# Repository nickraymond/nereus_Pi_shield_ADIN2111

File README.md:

# nereus_Pi_shield_ADIN2111

A Raspberry Pi Zero 2W shield built from a copy of the Sofar Bristlemouth mote:
ADIN2111 two-port 10BASE-T1L with PoDL, powered from the bus, 5 V for the Pi,
a 24 V payload port, and the Sofar mote's power path unchanged except the payload load switch (D17) (~20 W absolute
max, 890 mA per port inductor at 24 V; 50 W in a later revision). Potted.

Claude Code does the schematic capture, up to a design-review package. Nick
reviews, lays out, routes and brings up the board.

## Folders

```
Nereus_Pi_Shield_Adin2111/   live KiCad 10 project, the board ordered at JLC — open Nereus_Pi_Shield_Adin2111.kicad_pro
docs/                        spec, tracker, design log, power-path study
docs/design-review/          ERC, netlist, PDF and the review package
KiCAD_reference_designs/     BM mote 000639-AB, UrchinCam (read-only)
Archive/                     earlier iterations, junction fix (read-only)
pi-shield-checklist.html     shared visual view of docs/TRACKER.md (open in a browser)
```

## Working on it

- Agents: start with `CLAUDE.md`, then `/agent-entry`.
- People: `docs/TRACKER.md` shows where things stand; `docs/SPEC.md` says what
  we're building and why.
- Close KiCad before an agent edits the project.

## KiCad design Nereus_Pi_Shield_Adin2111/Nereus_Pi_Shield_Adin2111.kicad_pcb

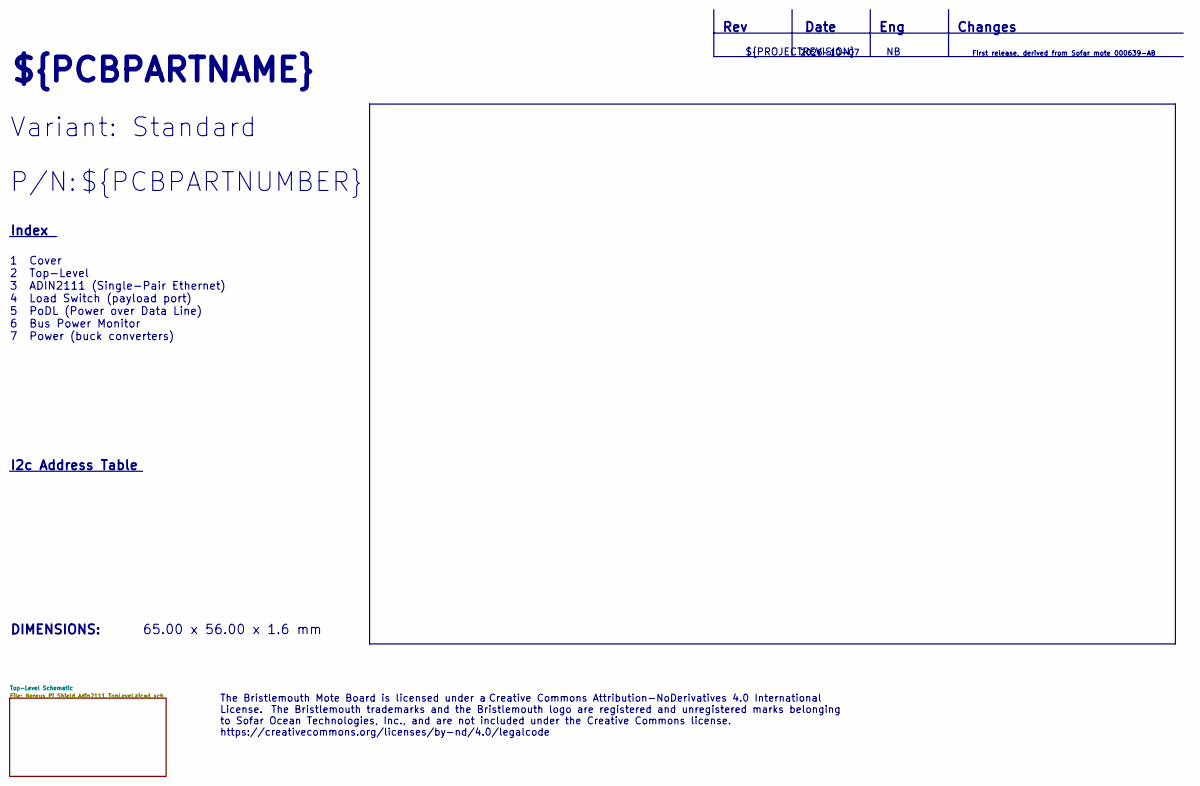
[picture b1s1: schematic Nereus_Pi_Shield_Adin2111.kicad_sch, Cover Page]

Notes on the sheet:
Variant: Standard
Date
${PCBPARTNAME}
Changes
${PCBPARTNUMBER}
First release, derived from Sofar mote 000639-AB
Index
2026-10-07
${PROJECTREVISION}
Rev
I2c Address Table
Eng
65.00 x 56.00 x 1.6 mm
1 Cover 2 Top-Level 3 ADIN2111 (Single-Pair Ethernet) 4 Load Switch (payload port) 5 PoDL (Power over Data Line) 6 Bus Power Monitor 7 Power (buck converters)
P/N:
DIMENSIONS:
The Bristlemouth Mote Board is licensed under a Creative Commons Attribution-NoDerivatives 4.0 International License. The Bristlemouth trademarks and the Bristlemouth logo are registered and unregistered marks belonging to Sofar Ocean Technologies, Inc., and are not included under the Creative Comm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

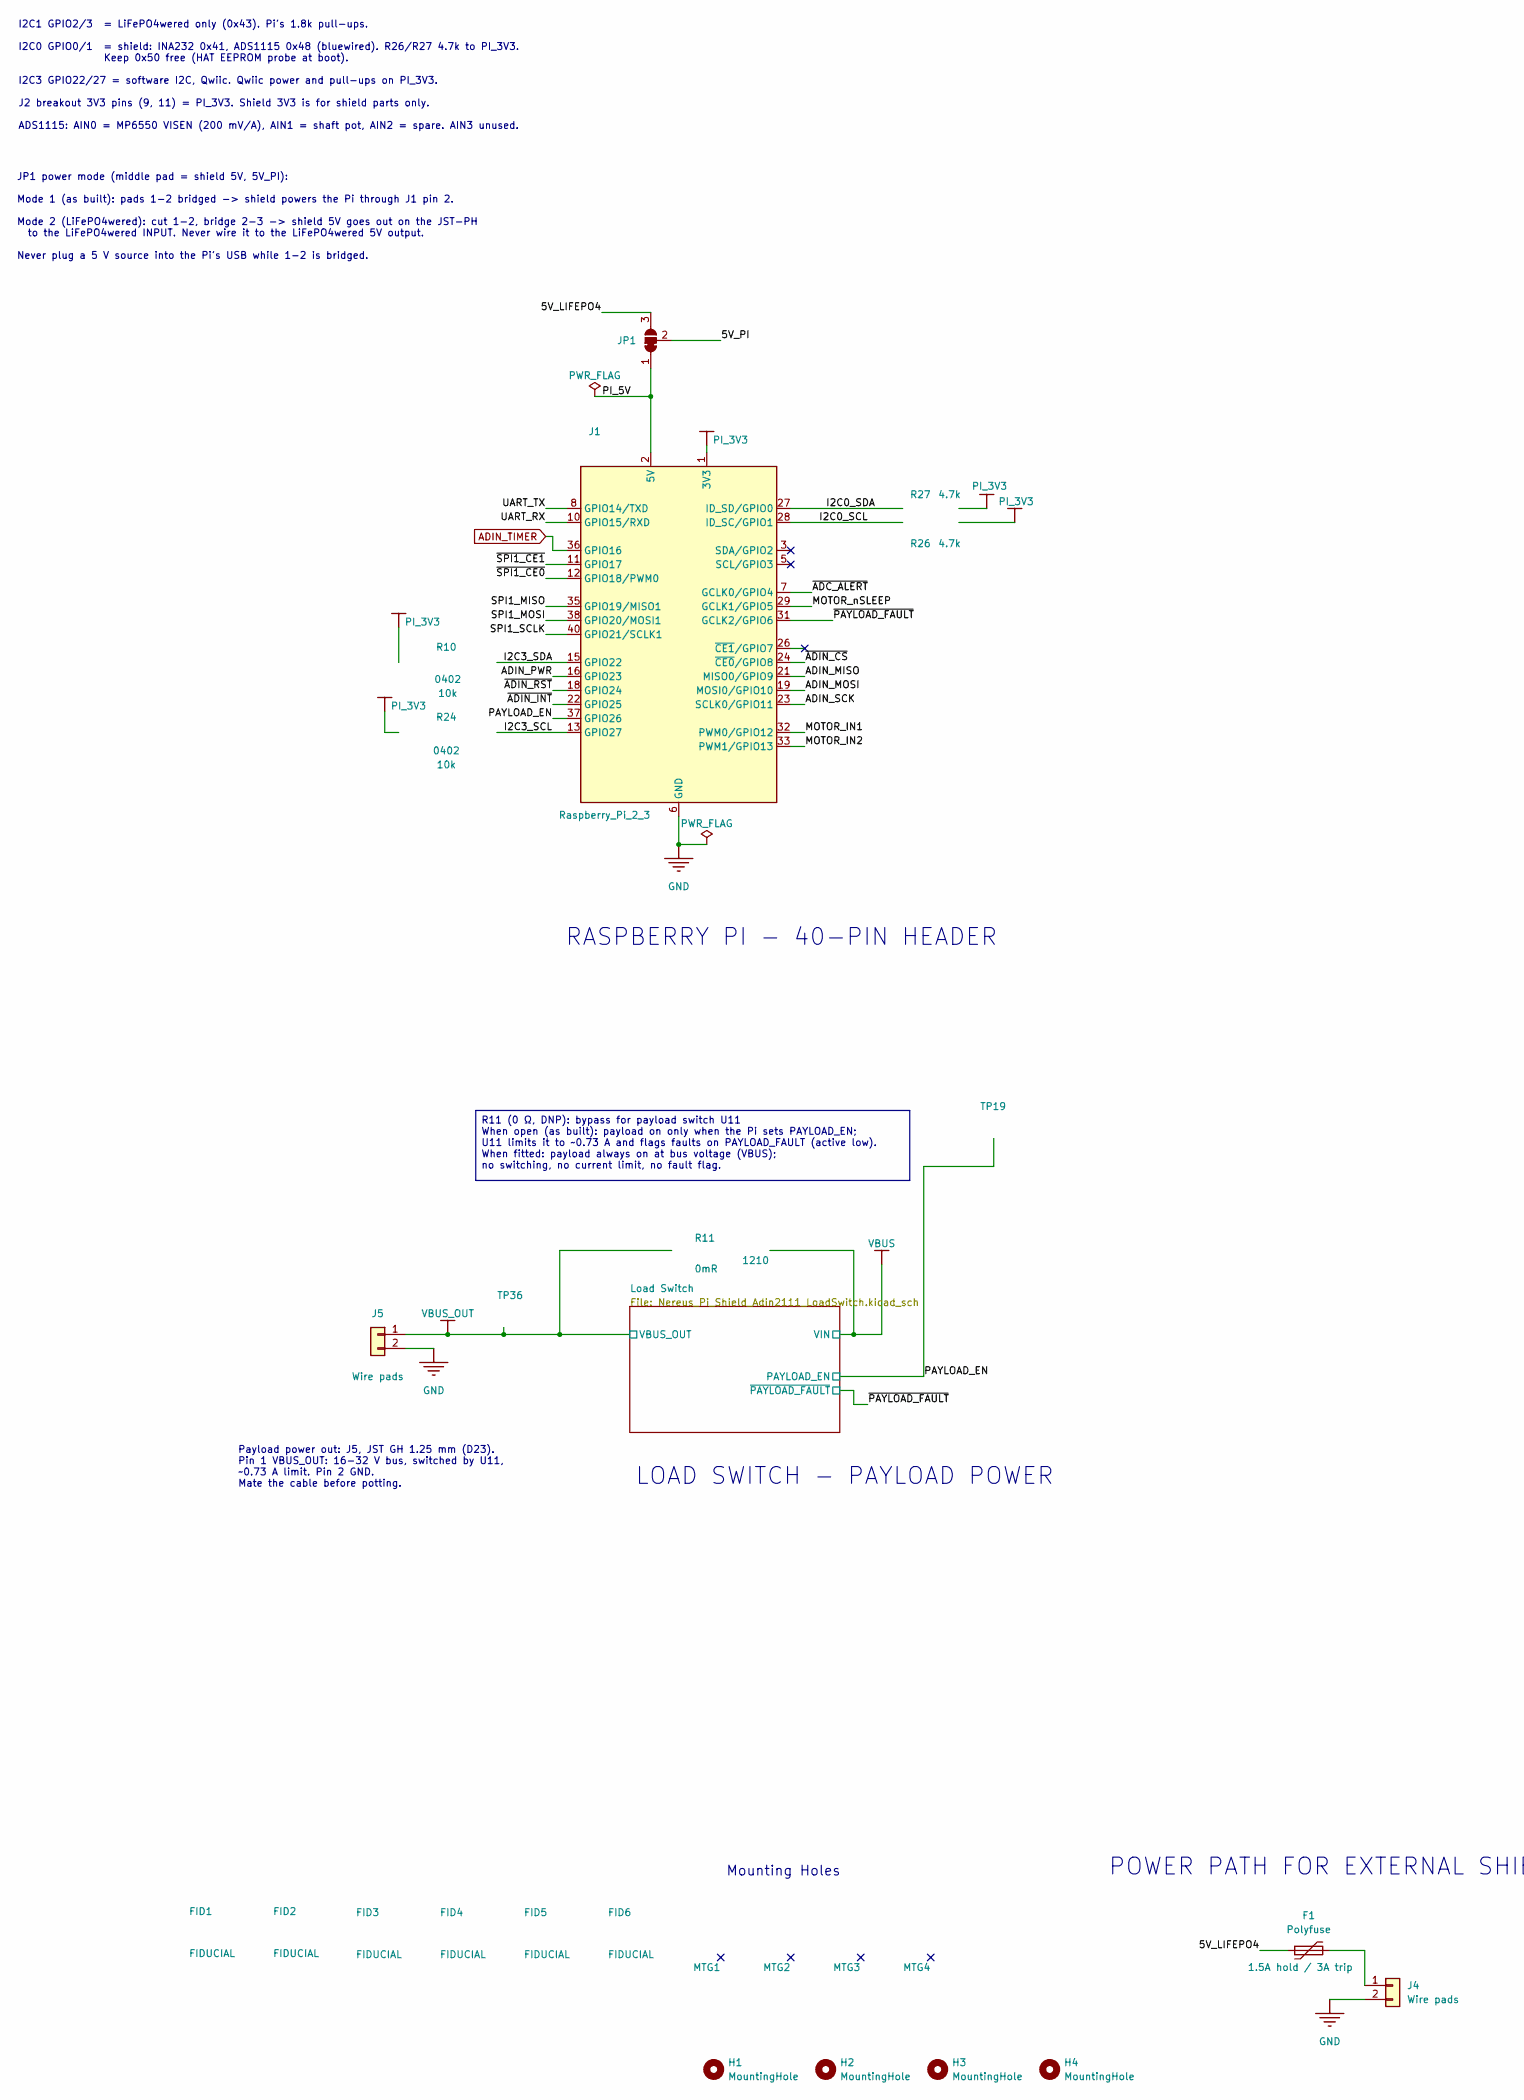
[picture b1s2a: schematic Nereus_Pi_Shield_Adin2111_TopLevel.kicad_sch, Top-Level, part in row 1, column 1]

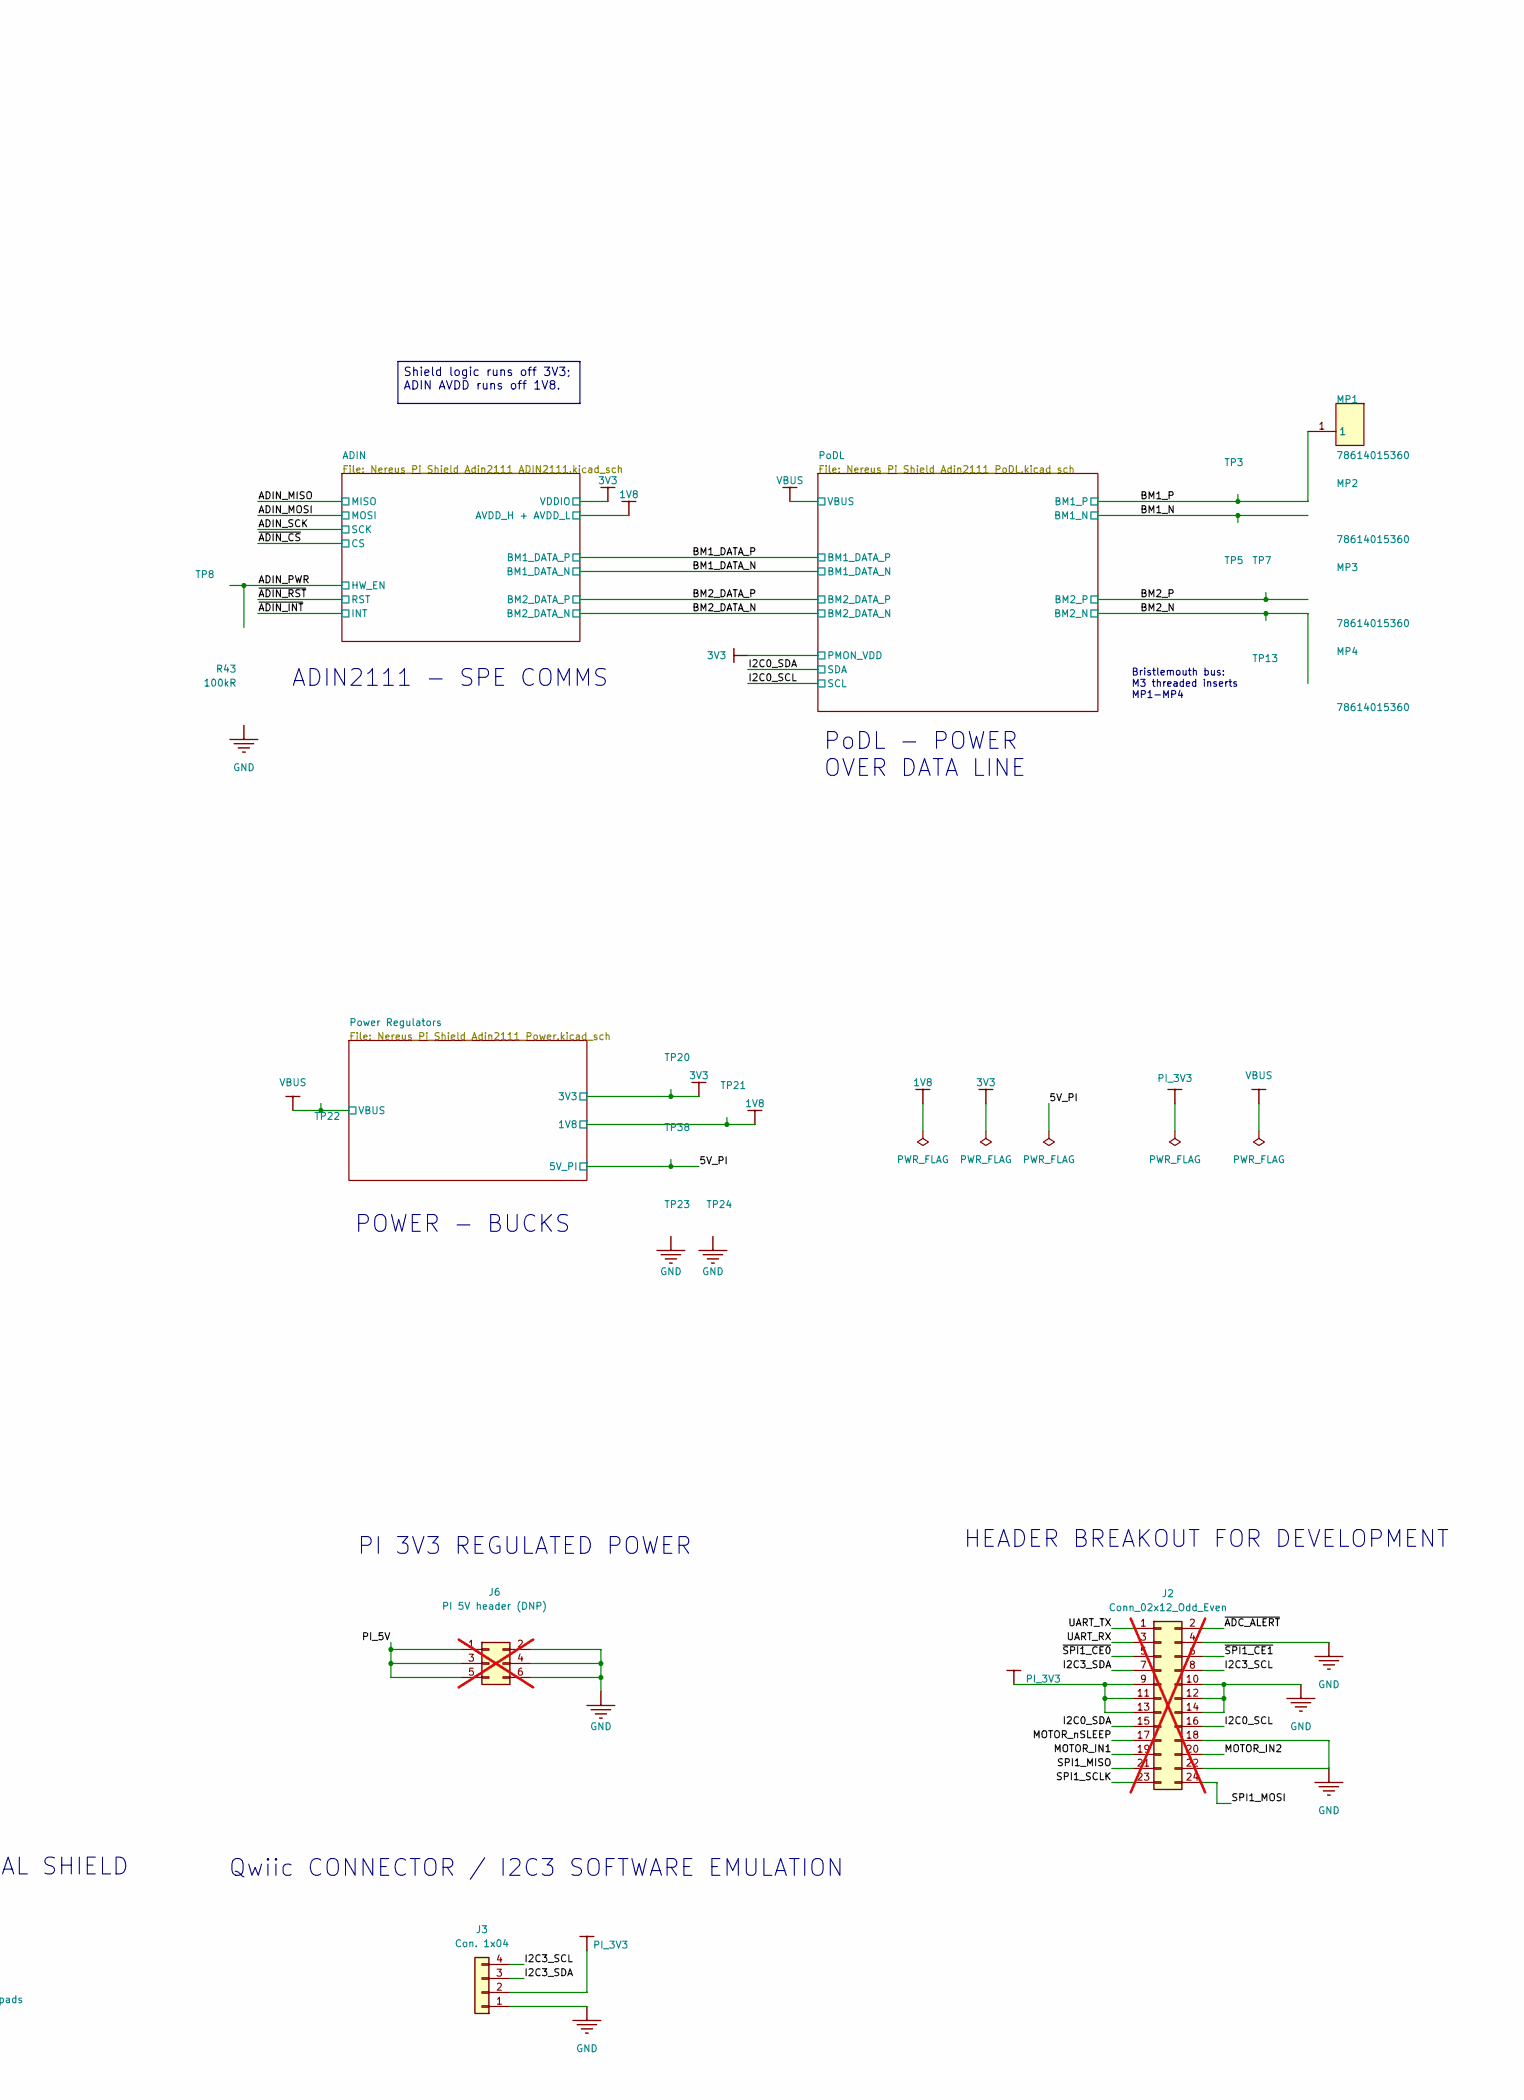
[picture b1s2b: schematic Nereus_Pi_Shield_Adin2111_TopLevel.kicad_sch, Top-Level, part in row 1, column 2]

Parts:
F1: Polyfuse; Fuse_1206_3216Metric
FID1, FID2, FID3, FID4, FID5, FID6: FIDUCIAL; FIDUCIAL_075MM
H1, H2, H3, H4: MountingHole; MountingHole_2.7mm_M2.5_ISO7380
J1: Raspberry_Pi_2_3; PinSocket_2x20_P2.54mm_Vertical
J2: Conn_02x12_Odd_Even; PinHeader_2x12_P2.54mm_Vertical; not fitted
J3: Con. 1x04; JST_SH_SM04B-SRSS-TB_1x04-1MP_P1.00mm_Horizontal
J4, J5: Wire pads; WirePads_1x02_P3.81mm_Oval4.2x2.6mm_Drill1.3mm
J6: PI 5V header (DNP); PinHeader_2x03_P2.54mm_Vertical; not fitted
JP1: SolderJumper_3_Bridged12; SolderJumper-3_P1.3mm_Bridged12_RoundedPad1.0x1.5mm
MP1, MP2, MP3, MP4: 78614015360; 78614015360-Footprint-2; MANUFACTURER PART NUMBER 78614015360
MTG1, MTG2, MTG3, MTG4: Hole_M3
R10, R24: RC0402JR-0710KL; FP-RC0402-0_4-IPC_C; RESISTANCE TOLERANCE 5%; POWER RATING 62.5mW
R11: CRCW12100000Z0EA; FP-CRCW1210-e3-IPC_B; POWER RATING 500mW; VOLTAGE RATING 200V; not fitted
R26, R27: ERJ-2RKF4701X; RESC1005X40X25LL05T05; TOLERANCE 1%; VOLTAGE RATING 50 V; PARTNUMBER ERJ-2RKF4701X
R43: RMCF0402FT100K; FP-RMCF0402-IPC_C; TOLERANCE 1%; POWER RATING 62.5mW
TP3, TP5, TP7, TP8, TP13, TP19, TP20, TP21, TP22, TP23, TP24, TP36, TP38: TEST_POINT; PCB_TP_1.5mm; PARTTYPE non BOM

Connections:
1V8: TP21.1 (1_1); also elsewhere on the board
3V3: TP20.1 (1_1); also elsewhere on the board
/Top-Level Schematic/5V_LIFEPO4: F1.1, JP1.3 (B)
/Top-Level Schematic/5V_PI: JP1.2 (C), TP38.1 (1_1); also elsewhere on the board
/Top-Level Schematic/ADIN_MISO: J1.21 (MISO0/GPIO9); also elsewhere on the board
/Top-Level Schematic/ADIN_MOSI: J1.19 (MOSI0/GPIO10); also elsewhere on the board
/Top-Level Schematic/ADIN_PWR: J1.16 (GPIO23), R43.1, TP8.1 (1_1); also elsewhere on the board
/Top-Level Schematic/ADIN_SCK: J1.23 (SCLK0/GPIO11); also elsewhere on the board
/Top-Level Schematic/BM1_N: MP2.1 (1_1), TP5.1 (1_1); also elsewhere on the board
/Top-Level Schematic/BM1_P: MP1.1 (1_1), TP3.1 (1_1); also elsewhere on the board
/Top-Level Schematic/BM2_N: MP4.1 (1_1), TP13.1 (1_1); also elsewhere on the board
/Top-Level Schematic/BM2_P: MP3.1 (1_1), TP7.1 (1_1); also elsewhere on the board
/Top-Level Schematic/I2C0_SCL: J1.28 (ID_SC/GPIO1), J2.16, R26.1; also elsewhere on the board
/Top-Level Schematic/I2C0_SDA: J1.27 (ID_SD/GPIO0), J2.15, R27.1; also elsewhere on the board
/Top-Level Schematic/I2C3_SCL: J1.13 (GPIO27), J2.8, J3.4, R24.1
/Top-Level Schematic/I2C3_SDA: J1.15 (GPIO22), J2.7, J3.3, R10.1
/Top-Level Schematic/MOTOR_IN1: J1.32 (PWM0/GPIO12), J2.19
/Top-Level Schematic/MOTOR_IN2: J1.33 (PWM1/GPIO13), J2.20
/Top-Level Schematic/MOTOR_nSLEEP: J1.29 (GCLK1/GPIO5), J2.17
/Top-Level Schematic/PAYLOAD_EN: J1.37 (GPIO26), TP19.1 (1_1); also elsewhere on the board
/Top-Level Schematic/PI_5V: J1.2 (5V), J1.4 (5V), J6.1, J6.3, J6.5, JP1.1 (A)
/Top-Level Schematic/SPI1_MISO: J1.35 (GPIO19/MISO1), J2.21
/Top-Level Schematic/SPI1_MOSI: J1.38 (GPIO20/MOSI1), J2.24
/Top-Level Schematic/SPI1_SCLK: J1.40 (GPIO21/SCLK1), J2.23
/Top-Level Schematic/UART_RX: J1.10 (GPIO15/RXD), J2.3
/Top-Level Schematic/UART_TX: J1.8 (GPIO14/TXD), J2.1
/Top-Level Schematic/~ADC_ALERT: J1.7 (GCLK0/GPIO4), J2.2
/Top-Level Schematic/~ADIN_CS: J1.24 (~CE0/GPIO8); also elsewhere on the board
/Top-Level Schematic/~ADIN_INT: J1.22 (GPIO25); also elsewhere on the board
/Top-Level Schematic/~ADIN_RST: J1.18 (GPIO24); also elsewhere on the board
/Top-Level Schematic/~PAYLOAD_FAULT: J1.31 (GCLK2/GPIO6); also elsewhere on the board
/Top-Level Schematic/~SPI1_CE0: J1.12 (GPIO18/PWM0), J2.5
/Top-Level Schematic/~SPI1_CE1: J1.11 (GPIO17), J2.6
ADIN_TIMER: J1.36 (GPIO16); also elsewhere on the board
GND: J1.6 (GND), J1.9 (GND), J1.14 (GND), J1.20 (GND), J1.25 (GND), J1.30 (GND), J1.34 (GND), J1.39 (GND), J2.4, J2.10, J2.12, J2.14, J2.18, J2.22, J3.1, J4.2, J5.2, J6.2, J6.4, J6.6, R43.2, TP23.1 (1_1), TP24.1 (1_1); also elsewhere on the board
unnamed: F1.2, J4.1
PI_3V3: J1.1 (3V3), J1.17 (3V3), J2.9, J2.11, J2.13, J3.2, R10.2, R24.2, R26.2, R27.2
VBUS: R11.1, TP22.1 (1_1); also elsewhere on the board
VBUS_OUT: J5.1, R11.2, TP36.1 (1_1); also elsewhere on the board

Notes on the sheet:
JP1 power mode (middle pad = shield 5V, 5V_PI): Mode 1 (as built): pads 1-2 bridged -> shield powers the Pi through J1 pin 2. Mode 2 (LiFePO4wered): cut 1-2, bridge 2-3 -> shield 5V goes out on the JST-PH to the LiFePO4wered INPUT. Never wire it to the LiFePO4wered 5V output. Never plug a 5 V sourc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
I2C1 GPIO2/3 = LiFePO4wered only (0x43). Pi's 1.8k pull-ups. I2C0 GPIO0/1 = shield: INA232 0x41, ADS1115 0x48 (bluewired). R26/R27 4.7k to PI_3V3. Keep 0x50 free (HAT EEPROM probe at boot). I2C3 GPIO22/27 = software I2C, Qwiic. Qwiic power and pull-ups on PI_3V3. J2 breakout 3V3 pins (9, 11) = PI_3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
Payload power out: J5, JST GH 1.25 mm (D23). Pin 1 VBUS_OUT: 16-32 V bus, switched by U11, ~0.73 A limit. Pin 2 GND. Mate the cable before potting.
Shield logic runs off 3V3; ADIN AVDD runs off 1V8.
LOAD SWITCH - PAYLOAD POWER
Qwiic CONNECTOR / I2C3 SOFTWARE EMULATION
RASPBERRY PI - 40-PIN HEADER
PoDL - POWER OVER DATA LINE
POWER PATH FOR EXTERNAL SHIELD
ADIN2111 - SPE COMMS
Bristlemouth bus: M3 threaded inserts MP1-MP4
R11 (0 Ω, DNP): bypass for payload switch U11 When open (as built): payload on only when the Pi sets PAYLOAD_EN; U11 limits it to ~0.73 A and flags faults on PAYLOAD_FAULT (active low). When fitted: payload always on at bus voltage (VBUS); no switching, no current limit, no fault flag.
HEADER BREAKOUT FOR DEVELOPMENT
Mounting Holes
PI 3V3 REGULATED POWER
POWER - BUCKS

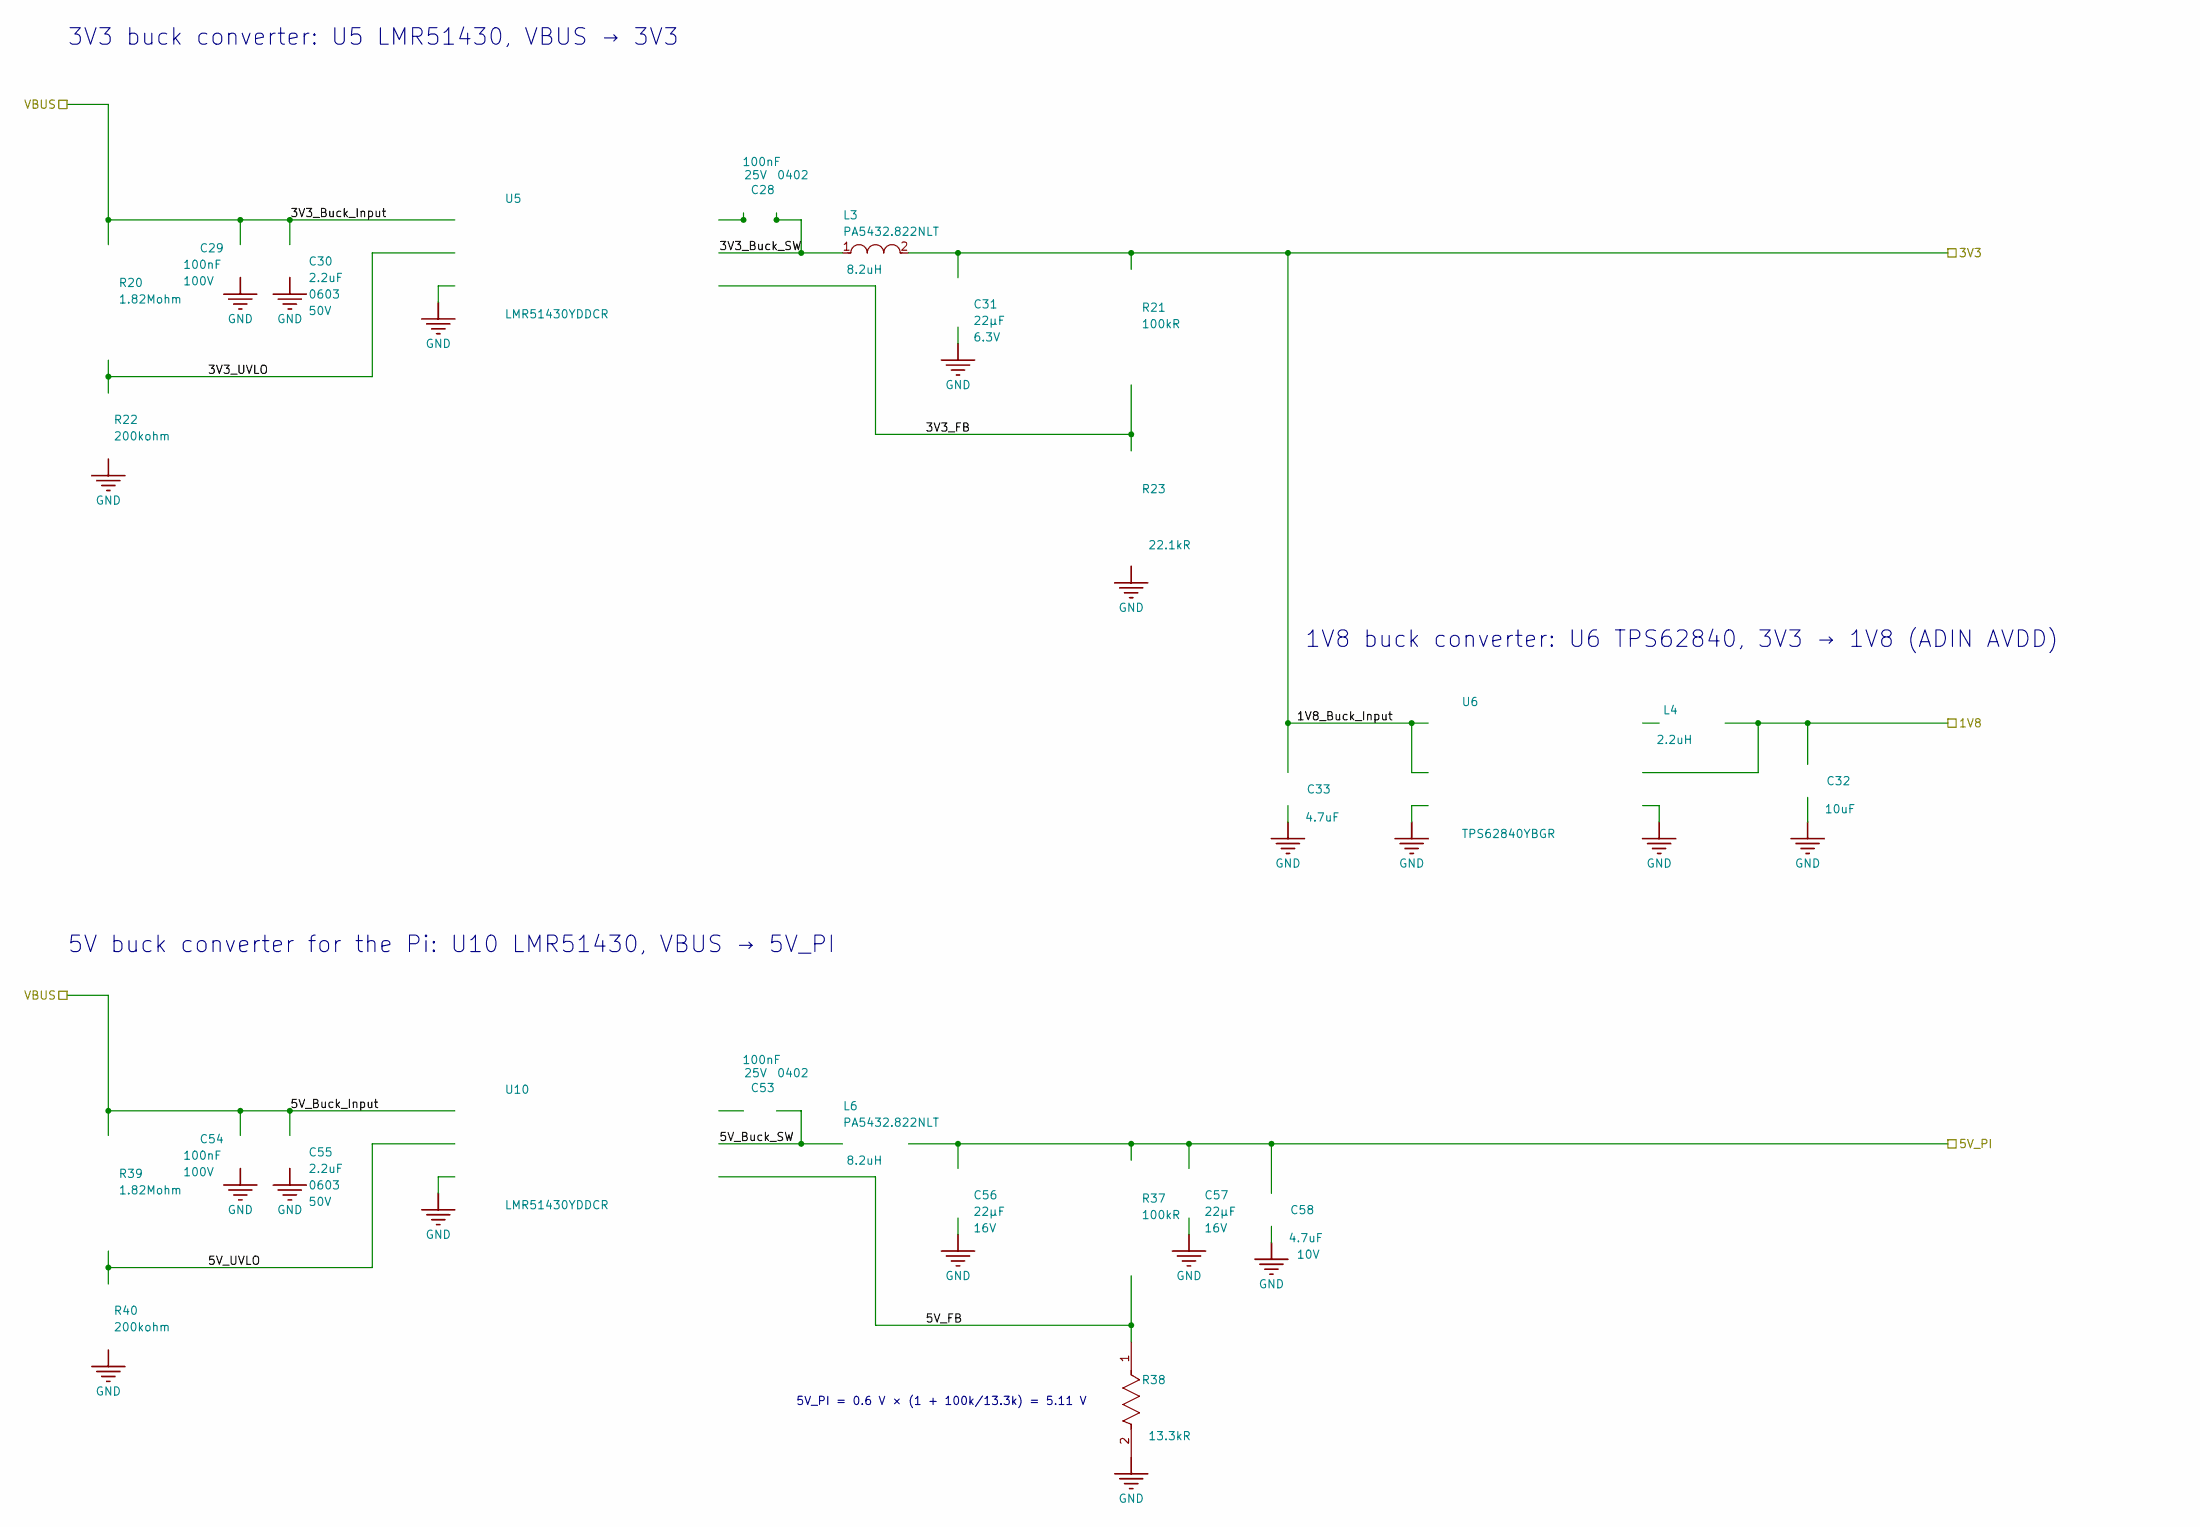
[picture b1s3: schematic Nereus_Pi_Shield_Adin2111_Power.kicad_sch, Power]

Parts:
C28, C53: CL05A104KA5NNNC; FP-CL278-IPC_C; VOLTAGE 25V; VOLTAGE RATING 25V
C29, C54: GRM188R72A104KA35D; FP-GRM188-0_1-e0_2_0_5-IPC_B; VOLTAGE RATING (DC) 100V; VOLTAGE 100V
C30, C55: UMK107BBJ225KA-T; FP-0603-L_1_6_0_2-W_0_8_0-MFG; VOLTAGE RATING 50V; TOLERANCE 10%
C31: C1608X5R0J226M080AC; CAPC1608X100X20ML10; TOLERANCE ±20%; VOLTAGE - RATED 6.3V
C32: GRJ155R60J106ME11D; FP-GRJ155-0_2-MFG; TOLERANCE 20%; VOLTAGE RATING 6.3V
C33: GRM155R60J475ME87D; FP-GRM155-0_15-MFG; TOLERANCE 20%; VOLTAGE 6.3V
C56, C57: GRM21BR61C226ME44L; C_0805_2012Metric; TOLERANCE ±20%; VOLTAGE - RATED 16V
C58: GRM155R61A475MEAAD; C_0402_1005Metric; TOLERANCE 20%; VOLTAGE RATING 10V
L3, L6: PA5432.822NLT; FP-PA5432_472NLT-MFG
L4: DFE201612E-2R2M=P2; FP-DFE201612C-MFG
R20, R39: CRCW04021M82FKED; FP-CRCW0402-e3-MFG; RESISTANCE TOLERANCE 1%; POWER RATING 63mW
R21, R37: RMCF0402FT100K; FP-RMCF0402-IPC_C; TOLERANCE 1%; POWER RATING 62.5mW
R22, R40: RC0402FR-07200KL; RESC1005X40X25LL05T10; PART NUMBER RC0402FR-07200KL
R23: RC0402FR-0722K1L; FP-RC0402-0_4-IPC_B; WORKING VOLTAGE 50V; RESISTANCE TOLERANCE 1%
R38: 0402WGF1332TCE; FP-RC0402-0_4-IPC_B; WORKING VOLTAGE 50V; RESISTANCE TOLERANCE 1%
U5, U10: LMR51430YDDCR; SOT-23-THIN-6_DDC_TEX; MANUFACTURER_PART_NUMBER LMR51430YDDCR
U6: TPS62840YBGR; FP-YBG0006-MFG

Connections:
1V8: C32.1, L4.2, U6.A2 (VOS); also elsewhere on the board
3V3: C31.2, C33.1, L3.2, R21.1, U6.B1 (VIN), U6.C1 (EN); also elsewhere on the board
/Top-Level Schematic/5V_PI: C56.2, C57.2, C58.1, L6.2, R37.1; also elsewhere on the board
/Top-Level Schematic/Power Regulators/3V3_Buck_SW: C28.1, L3.1, U5.2 (SW)
/Top-Level Schematic/Power Regulators/3V3_FB: R21.2, R23.1, U5.4 (FB)
/Top-Level Schematic/Power Regulators/3V3_UVLO: R20.1, R22.2, U5.5 (EN)
/Top-Level Schematic/Power Regulators/5V_Buck_SW: C53.1, L6.1, U10.2 (SW)
/Top-Level Schematic/Power Regulators/5V_FB: R37.2, R38.1, U10.4 (FB)
/Top-Level Schematic/Power Regulators/5V_UVLO: R39.1, R40.2, U10.5 (EN)
GND: C29.2, C30.2, C31.1, C32.2, C33.2, C54.2, C55.2, C56.1, C57.1, C58.2, R22.1, R23.2, R38.2, R40.1, U5.1 (GND), U6.A1 (GND), U6.C2 (VSET), U10.1 (GND); also elsewhere on the board
unnamed: C28.2, U5.6 (CB)
unnamed: L4.1, U6.B2 (SW)
unnamed: C53.2, U10.6 (CB)
VBUS: C29.1, C30.1, C54.1, C55.1, R20.2, R39.2, U5.3 (VIN), U10.3 (VIN); also elsewhere on the board

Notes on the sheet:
1V8 buck converter: U6 TPS62840, 3V3 → 1V8 (ADIN AVDD)
3V3 buck converter: U5 LMR51430, VBUS → 3V3
5V buck converter for the Pi: U10 LMR51430, VBUS → 5V_PI
5V_PI = 0.6 V × (1 + 100k/13.3k) = 5.11 V

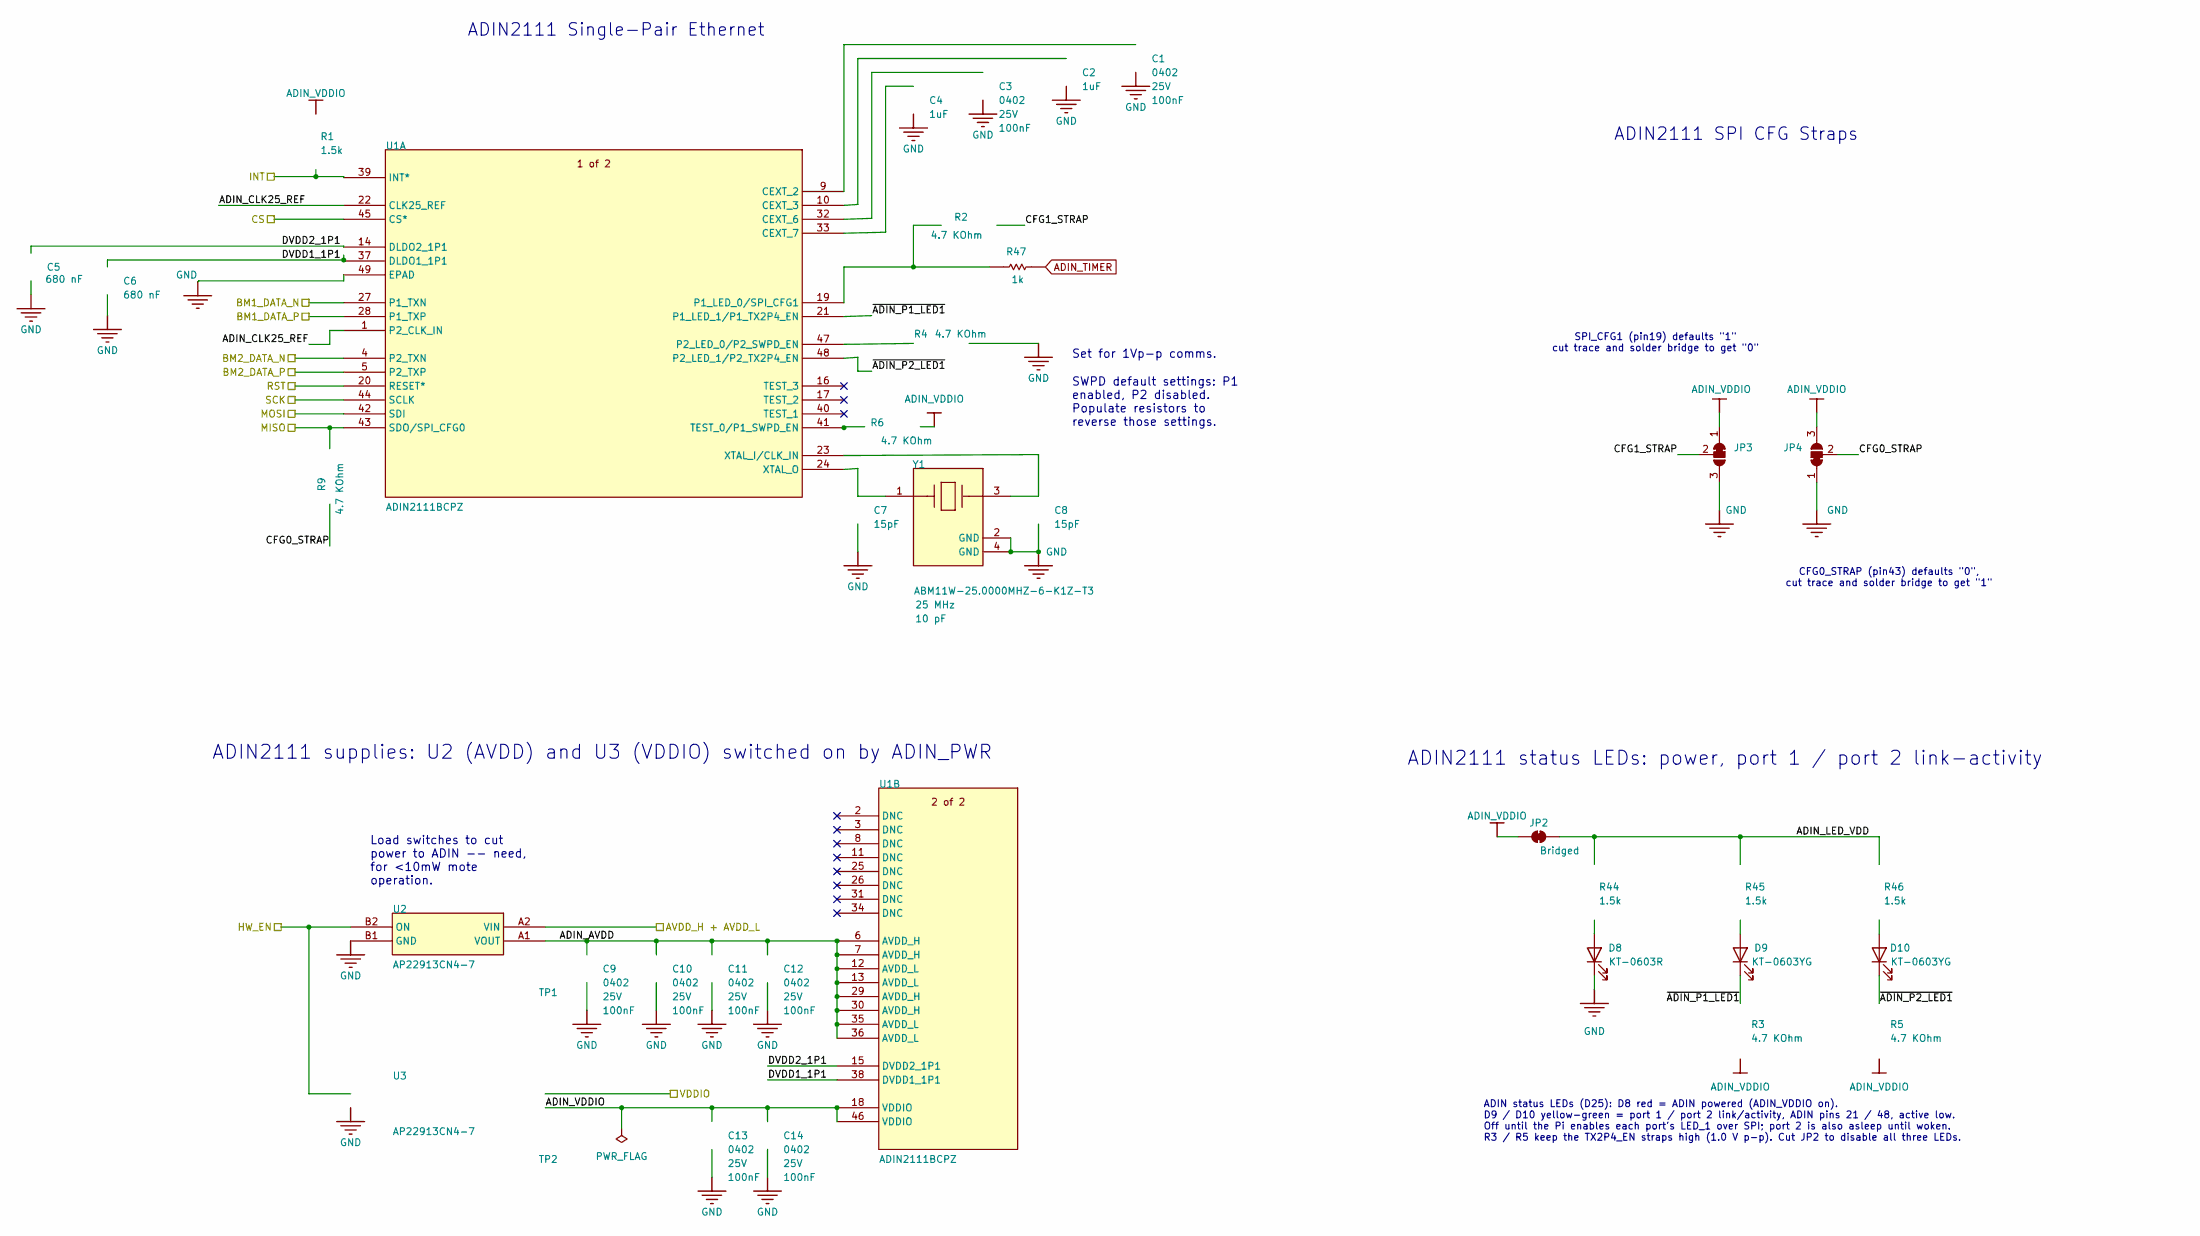
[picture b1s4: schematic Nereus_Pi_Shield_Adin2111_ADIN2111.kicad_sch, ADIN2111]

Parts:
C1, C3, C9, C10, C11, C12, C13, C14: CL05A104KA5NNNC; FP-CL278-IPC_C; VOLTAGE 25V; VOLTAGE RATING 25V
C2, C4: CL05A105KP5NNNC; FP-CL511-IPC_C; TOLERANCE 10%; VOLTAGE RATING 10V
C5, C6: CC0402KRX5R6BB684; FP-CC0402-MFG; TOLERANCE 0.1; VOLTAGE RATING 10 V; MANUFACTURER PART NUMBER CC0402KRX5R6BB684; DIGIKEY DESCRIPTION CAP CER 0.68UF 10V X5R 0402
C7, C8: CC0402JRNPO9BN150; FP-CC0402-0_55-IPC_B; VOLTAGE RATING (DC) 50V; VOLTAGE RATING 50V
D8: KT-0603R; LED_0603_1608Metric; LCSC C2286
D9, D10: KT-0603YG; LED_0603_1608Metric; LCSC C2289
JP2: Bridged; SolderJumper-2_R1210_Bridged_NetTie
JP3, JP4: SolderJumper_3_Bridged12; SolderJumper-3_P1.3mm_Bridged12_RoundedPad1.0x1.5mm
R1, R44, R45, R46: RC0402FR-071K5L; RESC1005X40X25ML05T10; PART NUMBER RC0402FR-071K5L
R2, R3, R4, R5, R6, R9: ERJ-2RKF4701X; RESC1005X40X25LL05T05; TOLERANCE 1%; VOLTAGE RATING 50 V; PARTNUMBER ERJ-2RKF4701X
R47: RC0402FR-071KL; RESC1005X40X25ML05T10; PART NUMBER RC0402FR-071KL
TP1, TP2: TEST_POINT; PCB_TP_1.5mm; PARTTYPE non BOM
U1: ADIN2111BCPZ; ADIN2111BCPZ-Footprint-1
U2, U3: AP22913CN4-7; AP22913CN4-7-Footprint-1
Y1: ABM11W-25.0000MHZ-6-K1Z-T3; FP-ABM11W-MFG

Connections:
1V8: U2.A2 (VIN); also elsewhere on the board
3V3: U3.A2 (VIN); also elsewhere on the board
/Top-Level Schematic/ADIN/ADIN_AVDD: C9.1, C10.1, C11.1, C12.1, TP1.1 (1_1), U1.6 (AVDD_H), U1.7 (AVDD_H), U1.12 (AVDD_L), U1.13 (AVDD_L), U1.29 (AVDD_H), U1.30 (AVDD_H), U1.35 (AVDD_L), U1.36 (AVDD_L), U2.A1 (VOUT)
/Top-Level Schematic/ADIN/ADIN_CLK25_REF: U1.1 (P2_CLK_IN), U1.22 (CLK25_REF)
/Top-Level Schematic/ADIN/ADIN_LED_VDD: JP2.2 (B), R44.2, R45.2, R46.2
/Top-Level Schematic/ADIN/CFG0_STRAP: JP4.2 (C), R9.1
/Top-Level Schematic/ADIN/CFG1_STRAP: JP3.2 (C), R2.2
/Top-Level Schematic/ADIN/DVDD1_1P1: C6.1, U1.37 (DLDO1_1P1), U1.38 (DVDD1_1P1)
/Top-Level Schematic/ADIN/DVDD2_1P1: C5.1, U1.14 (DLDO2_1P1), U1.15 (DVDD2_1P1)
/Top-Level Schematic/ADIN/~ADIN_P1_LED1: D9.1 (K), R3.1, U1.21 (P1_LED_1/P1_TX2P4_EN)
/Top-Level Schematic/ADIN/~ADIN_P2_LED1: D10.1 (K), R5.1, U1.48 (P2_LED_1/P2_TX2P4_EN)
/Top-Level Schematic/ADIN_MISO: R9.2, U1.43 (SDO/SPI_CFG0); also elsewhere on the board
/Top-Level Schematic/ADIN_MOSI: U1.42 (SDI); also elsewhere on the board
/Top-Level Schematic/ADIN_PWR: U2.B2 (ON), U3.B2 (ON); also elsewhere on the board
/Top-Level Schematic/ADIN_SCK: U1.44 (SCLK); also elsewhere on the board
/Top-Level Schematic/BM1_DATA_N: U1.27 (P1_TXN); also elsewhere on the board
/Top-Level Schematic/BM1_DATA_P: U1.28 (P1_TXP); also elsewhere on the board
/Top-Level Schematic/BM2_DATA_N: U1.4 (P2_TXN); also elsewhere on the board
/Top-Level Schematic/BM2_DATA_P: U1.5 (P2_TXP); also elsewhere on the board
/Top-Level Schematic/~ADIN_CS: U1.45 (CS*); also elsewhere on the board
/Top-Level Schematic/~ADIN_INT: R1.1, U1.39 (INT*); also elsewhere on the board
/Top-Level Schematic/~ADIN_RST: U1.20 (RESET*); also elsewhere on the board
ADIN_TIMER: R47.1; also elsewhere on the board
ADIN_VDDIO: C13.1, C14.1, JP2.1 (A), JP3.1 (A), JP4.3 (B), R1.2, R3.2, R5.2, R6.2, TP2.1 (1_1), U1.18 (VDDIO), U1.46 (VDDIO), U3.A1 (VOUT)
GND: C1.2, C2.2, C3.2, C4.2, C5.2, C6.2, C7.2, C8.2, C9.2, C10.2, C11.2, C12.2, C13.2, C14.2, D8.1 (K), JP3.3 (B), JP4.1 (A), R4.2, U1.49 (EPAD), U2.B1 (GND), U3.B1 (GND), Y1.2 (GND), Y1.4 (GND); also elsewhere on the board
unnamed: D8.2 (A), R44.1
unnamed: D9.2 (A), R45.1
unnamed: D10.2 (A), R46.1
unnamed: C1.1, U1.9 (CEXT_2)
unnamed: C2.1, U1.10 (CEXT_3)
unnamed: C3.1, U1.32 (CEXT_6)
unnamed: C4.1, U1.33 (CEXT_7)
unnamed: R2.1, R47.2, U1.19 (P1_LED_0/SPI_CFG1)
unnamed: R4.1, U1.47 (P2_LED_0/P2_SWPD_EN)
unnamed: R6.1, U1.41 (TEST_0/P1_SWPD_EN)
unnamed: C8.1, U1.23 (XTAL_I/CLK_IN), Y1.3
unnamed: C7.1, U1.24 (XTAL_O), Y1.1

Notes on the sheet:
ADIN2111 status LEDs: power, port 1 / port 2 link-activity
ADIN2111 supplies: U2 (AVDD) and U3 (VDDIO) switched on by ADIN_PWR
CFG0_STRAP (pin43) defaults "0", cut trace and solder bridge to get "1"
ADIN status LEDs (D25): D8 red = ADIN powered (ADIN_VDDIO on). D9 / D10 yellow-green = port 1 / port 2 link/activity, ADIN pins 21 / 48, active low. Off until the Pi enables each port's LED_1 over SPI; port 2 is also asleep until woken. R3 / R5 keep the TX2P4_EN straps high (1.0 V p-p). Cut JP2 to 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
SPI_CFG1 (pin19) defaults "1" cut trace and solder bridge to get "0"
Set for 1Vp-p comms.
Load switches to cut power to ADIN -- need, for <10mW mote operation.
ADIN2111 SPI CFG Straps
ADIN2111 Single-Pair Ethernet
SWPD default settings: P1 enabled, P2 disabled. Populate resistors to reverse those settings.

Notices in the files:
Nereus_Pi_Shield_Adin2111/Nereus_Pi_Shield_Adin2111.kicad_sch:
https://creativecommons.org/licenses/by-nd/4.0/legalcode
parts and their libraries:
Copyright(c) 2012 TAIYO YUDEN CO.,LTD. All Rights Reserved.\r
COPYRIGHT: Copyright (C) 2023 Ultra Librarian. All rights reserved.
